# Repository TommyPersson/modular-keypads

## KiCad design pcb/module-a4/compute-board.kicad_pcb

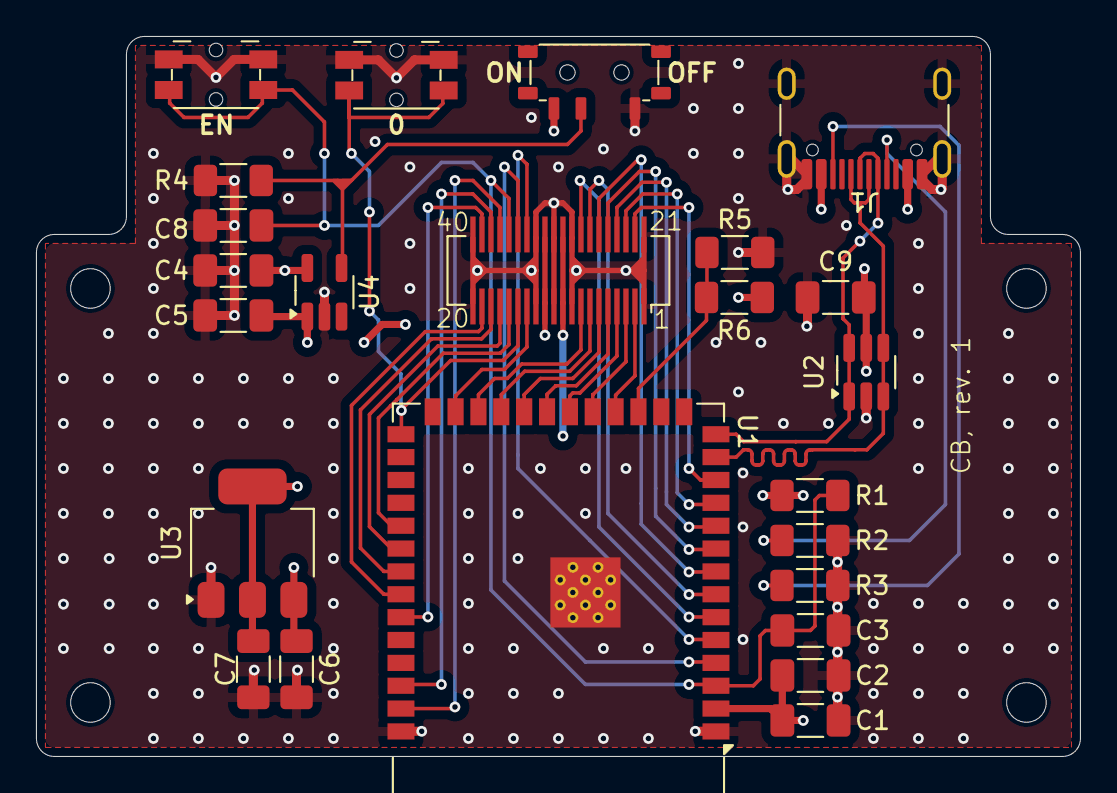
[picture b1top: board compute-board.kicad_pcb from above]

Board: 4 copper layers, 58.0 x 40.0 mm, 28 parts (0 on the bottom side), 36 nets.

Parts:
C1, C7: 22uF; C_1206_3216Metric_Pad1.33x1.80mm_HandSolder
C2, C4, C5, C8, C9: 0.1uF; C_1206_3216Metric_Pad1.33x1.80mm_HandSolder
C3: 1uF; C_1206_3216Metric_Pad1.33x1.80mm_HandSolder
C6: 10uF; C_1206_3216Metric_Pad1.33x1.80mm_HandSolder
H1, H2, H3, H4: MountingHole; MountingHole_2.2mm_M2
J1: USB_C_Receptacle_USB2.0_16P; USB_C_Receptacle_GCT_USB4105-xx-A_16P_TopMnt_Horizontal
J2: Conn_02x20; Hirose_DF12_DF12C3.0-40DS-0.5V_2x20_P0.50mm_Vertical
R1, R4, R5: 10k; R_1206_3216Metric_Pad1.30x1.75mm_HandSolder
R2, R3: 5.1K; R_1206_3216Metric_Pad1.30x1.75mm_HandSolder
R6: 5.1k; R_1206_3216Metric_Pad1.30x1.75mm_HandSolder
SW1: SW_Push_SPDT; SW_MSK12C02-HB
SW2, SW3: SW_Push; Panasonic_EVQPUL_EVQPUC
U1: ESP32-S3-WROOM-1
U2: USBLC6-2SC6; SOT-23-6_Handsoldering
U3: LD1117-3.3H; SOT-223-3_TabPin2
U4: AP2151W; SOT-23-5_HandSoldering

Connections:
+3.3V: C1.1, C2.1, C7.1, J2.10, J2.30, R1.1, U1.2 (3V3), U3.2 (VO)
+5V: C5.1, C6.1, J2.12, J2.32, U3.3 (VI), U4.1 (OUT)
/EN: C3.1, C8.2, J2.36, R1.2, SW2.2, U1.3 (EN)
/EX1: J2.7, U1.23 (IO21)
/EX2: J2.8, U1.24 (IO47)
/IO0: J2.15, SW3.2, U1.27 (IO0)
/IO1: J2.37, U1.39 (IO1)
/IO2: J2.38, U1.38 (IO2)
/IO4: J2.35, U1.4 (IO4)
/IO5: J2.34, U1.5 (IO5)
/IO6: J2.28, U1.6 (IO6)
/IO7: J2.27, U1.7 (IO7)
/IO8: J2.22, U1.12 (IO8)
/IO15: J2.26, U1.8 (IO15)
/IO16: J2.25, U1.9 (IO16)
/IO17: J2.24, U1.10 (IO17)
/IO18: J2.23, U1.11 (IO18)
/IO38: J2.16, U1.31 (IO38)
/IO39: J2.17, U1.32 (IO39)
/IO40: J2.18, U1.33 (IO40)
/IO41: J2.19, U1.34 (IO41)
/IO42: J2.39, U1.35 (IO42)
/IO48: J2.14, U1.25 (IO48)
/MISO: J2.5, U1.21 (IO13)
/MOSI: J2.6, U1.22 (IO14)
/SCK: J2.4, U1.20 (IO12)
/SCL: J2.2, U1.18 (IO10)
/SDA: J2.3, U1.19 (IO11)
/VBUS_SENSE: R5.1, R6.2, U1.17 (IO9)
/power-distribution/AP_EN: R4.1, SW1.2 (B), U4.4 (EN)
/usb-c-connector/CC1: J1.A5 (CC1), R2.1
/usb-c-connector/CC2: J1.B5 (CC2), R3.1
GND: C1.2, C2.2, C3.2, C4.2, C5.2, C6.2, C7.2, C8.1, C9.2, J1.A1 (GND), J1.A12 (GND), J1.B1 (GND), J1.B12 (GND), J1.S1 (SHIELD), J2.1, J2.9, J2.11, J2.13, J2.20, J2.21, J2.29, J2.31, J2.33, J2.40, R2.2, R3.2, R4.2, R5.2, SW1.1 (A), SW2.1, SW3.1, U1.1 (GND), U1.40 (GND), U1.41 (GND), U2.2 (GND), U3.1 (GND), U4.2 (GND)
USB_D+: J1.A7 (D-), J1.B7 (D-), U1.14 (USB_D+), U2.1 (I/O1), U2.6 (I/O1)
USB_D-: J1.A6 (D+), J1.B6 (D+), U1.13 (USB_D-), U2.3 (I/O2), U2.4 (I/O2)
VBUS: C4.1, C9.1, J1.A4 (VBUS), J1.A9 (VBUS), J1.B4 (VBUS), J1.B9 (VBUS), R6.1, SW1.3 (C), U2.5 (VBUS), U4.5 (IN)

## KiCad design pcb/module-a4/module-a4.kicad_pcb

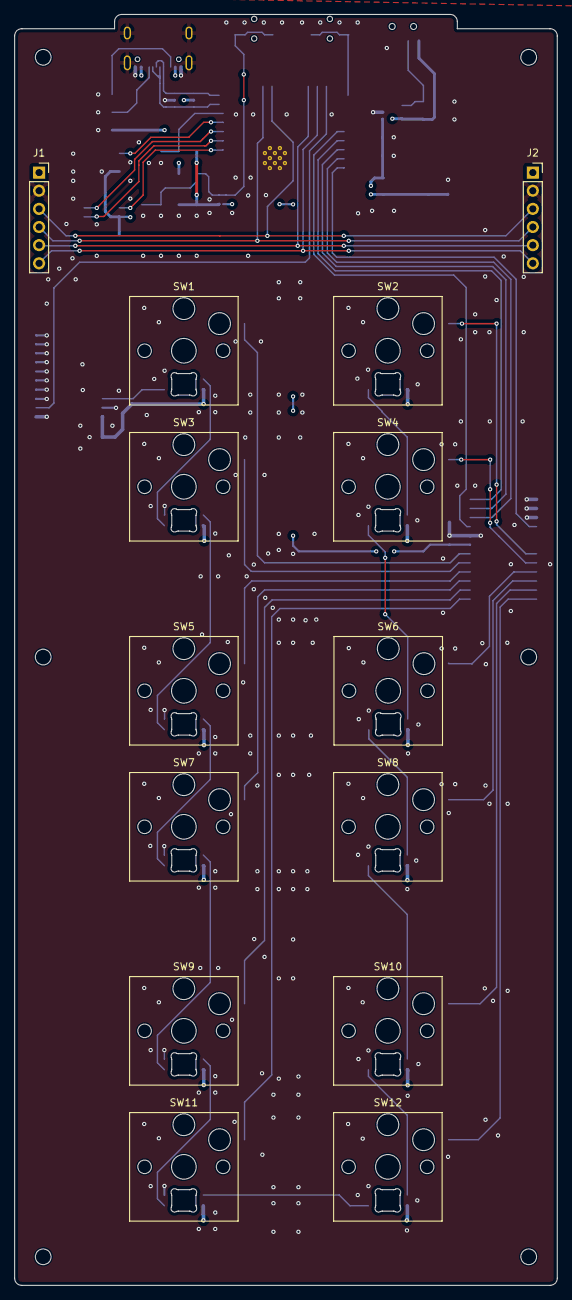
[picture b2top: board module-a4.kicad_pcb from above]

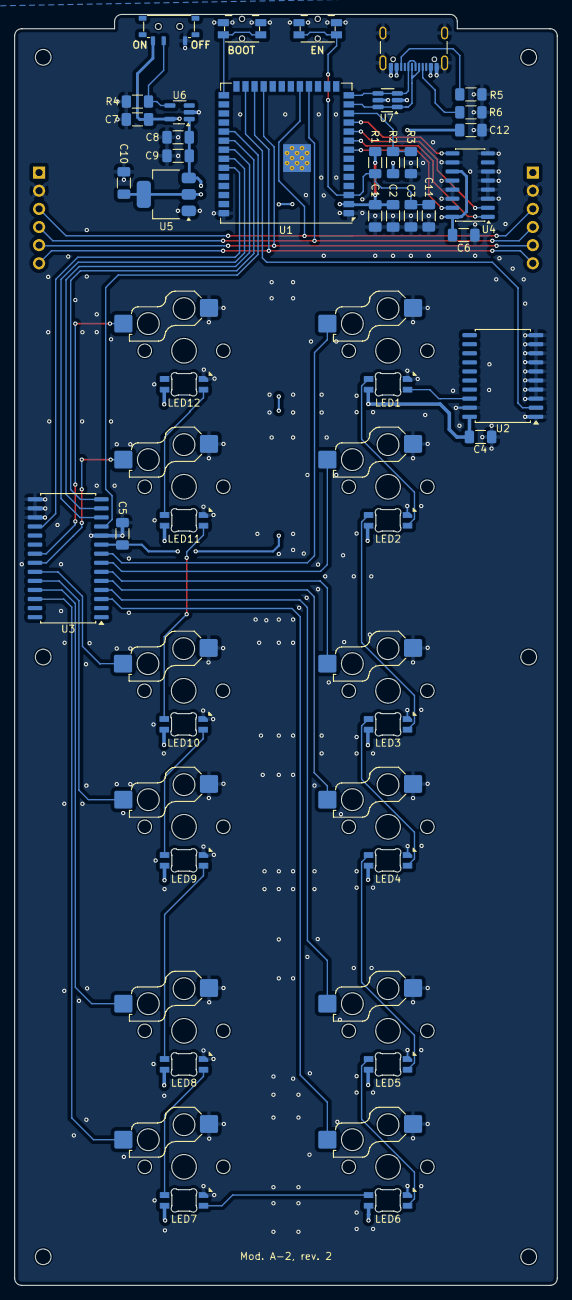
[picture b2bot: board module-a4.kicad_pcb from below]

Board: 4 copper layers, 76.0 x 178.0 mm, 61 parts (41 on the bottom side), 50 nets.

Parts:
C1, C10: 22uF; C_1206_3216Metric_Pad1.33x1.80mm_HandSolder
C2, C4, C5, C6, C7, C8, C11, C12: 0.1uF; C_1206_3216Metric_Pad1.33x1.80mm_HandSolder
C3: 1uF; C_1206_3216Metric_Pad1.33x1.80mm_HandSolder
C9: 10uF; C_1206_3216Metric_Pad1.33x1.80mm_HandSolder
H1, H2, H3, H4, H5, H6: MountingHole; MountingHole_2.2mm_M2
J1: Conn_01x06; PinSocket_1x06_P2.54mm_MagPogoHor_R
J2: Conn_01x06; PinSocket_1x06_P2.54mm_MagPogoHor
J3: USB_C_Receptacle_USB2.0_16P; USB_C_Receptacle_GCT_USB4105-xx-A_16P_TopMnt_Horizontal
LED1, LED2, LED3, LED4, LED5, LED6, LED7, LED8, LED9, LED10, LED11, LED12: SK6812MINI-E; LED_choc_6028R-ROT
R1, R3, R4: 10k; R_1206_3216Metric_Pad1.30x1.75mm_HandSolder
R2: 5.1k; R_1206_3216Metric_Pad1.30x1.75mm_HandSolder
R5, R6: 5.1K; R_1206_3216Metric_Pad1.30x1.75mm_HandSolder
SW1, SW2, SW3, SW4, SW5, SW6, SW7, SW8, SW9, SW10, SW11, SW12: SW_Push; SW_Hotswap_Kailh_Choc_V1_1.50u
SW13: SW_Push_SPDT; SW_MSK12C02-HB
SW14, SW15: SW_Push; Panasonic_EVQPUL_EVQPUC
U1: ESP32-S3-WROOM-1; ESP32-S3-WROOM-1U
U2: 74AHC541; SOIC-20W_7.5x12.8mm_P1.27mm
U3: MCP23S17_SO; SOIC-28W_7.5x17.9mm_P1.27mm
U4: 74HC165; SOIC-16_3.9x9.9mm_P1.27mm
U5: LD1117-3.3H; SOT-223-3_TabPin2
U6: AP2151W; SOT-23-5_HandSoldering
U7: USBLC6-2SC6; SOT-23-6_Handsoldering

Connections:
+3.3V: C1.1, C2.1, C5.1, C6.1, C10.1, R1.1, U1.2 (3V3), U3.9 (VDD), U4.11 (D0), U4.16 (VCC), U5.2 (VO)
+5V: C4.1, C8.1, C9.1, J1.1, J2.1, LED1.1 (VDD), LED2.1 (VDD), LED3.1 (VDD), LED4.1 (VDD), LED5.1 (VDD), LED6.1 (VDD), LED7.1 (VDD), LED8.1 (VDD), LED9.1 (VDD), LED10.1 (VDD), LED11.1 (VDD), LED12.1 (VDD), U2.20 (VCC), U5.3 (VI), U6.1 (OUT)
/A0: SW2.2, U3.21 (GPA0)
/A1: SW4.2, U3.22 (GPA1)
/A2: SW6.2, U3.23 (GPA2)
/A3: SW8.2, U3.24 (GPA3)
/A4: SW10.2, U3.25 (GPA4)
/A5: SW12.2, U3.26 (GPA5)
/B2: SW11.2, U3.3 (GPB2)
/B3: SW9.2, U3.4 (GPB3)
/B4: SW7.2, U3.5 (GPB4)
/B5: SW5.2, U3.6 (GPB5)
/B6: SW3.2, U3.7 (GPB6)
/B7: SW1.2, U3.8 (GPB7)
/EN: C3.1, C11.2, R1.2, SW14.2, U1.3 (EN)
/EX1: J1.5, J2.5, U1.23 (IO21)
/EX2: J1.6, J2.6, U1.24 (IO47)
/IO0: SW15.2, U1.27 (IO0)
/IO48: U1.25 (IO48), U2.2 (A0)
/MISO: U1.32 (IO39), U3.14 (SO)
/MOSI: U1.33 (IO40), U3.13 (SI)
/SCK: U1.34 (IO41), U3.12 (SCK)
/SCL: J1.4, J2.4, U1.18 (IO10)
/SDA: J1.3, J2.3, U1.19 (IO11)
/TREG_CP: U1.10 (IO17), U4.2 (CP)
/TREG_Q: U1.11 (IO18), U4.9 (Q7)
/VBUS_SENSE: R2.2, R3.1, U1.12 (IO8)
/power-distribution/AP_EN: R4.1, SW13.2 (B), U6.4 (EN)
/usb-c-connector/CC1: J3.A5 (CC1), R6.1
/usb-c-connector/CC2: J3.B5 (CC2), R5.1
/~MCP_CS: U1.31 (IO38), U3.11 (~CS)
/~MCP_RESET: U1.35 (IO42), U3.18 (~RESET)
/~TREG_CE: U1.8 (IO15), U4.15 (~CE)
/~TREG_PL: U1.9 (IO16), U4.1 (~PL)
GND: C1.2, C2.2, C3.2, C4.2, C5.2, C6.2, C7.2, C8.2, C9.2, C10.2, C11.1, C12.2, J1.2, J2.2, J3.A1 (GND), J3.A12 (GND), J3.B1 (GND), J3.B12 (GND), J3.S1 (SHIELD), LED1.4 (VSS), LED2.4 (VSS), LED3.4 (VSS), LED4.4 (VSS), LED5.4 (VSS), LED6.4 (VSS), LED7.4 (VSS), LED8.4 (VSS), LED9.4 (VSS), LED10.4 (VSS), LED11.4 (VSS), LED12.4 (VSS), R3.2, R4.2, R5.2, R6.2, SW1.1, SW2.1, SW3.1, SW4.1, SW5.1, SW6.1, SW7.1, SW8.1, SW9.1, SW10.1, SW11.1, SW12.1, SW13.1 (A), SW14.1, SW15.1, U1.1 (GND), U1.40 (GND), U1.41 (GND), U2.1 (G1), U2.3 (A1), U2.4 (A2), U2.5 (A3), U2.6 (A4), U2.7 (A5), U2.8 (A6), U2.9 (A7), U2.10 (GND), U2.19 (G2), U3.10 (VSS), U3.15 (A0), U3.16 (A1), U3.17 (A2), U4.3 (D4), U4.4 (D5), U4.5 (D6), U4.6 (D7), U4.8 (GND), U4.10 (DS), U4.12 (D1), U4.13 (D2), U4.14 (D3), U5.1 (GND), U6.2 (GND), U7.2 (GND)
unnamed: LED1.3 (DIN), U2.18 (Y0)
unnamed: LED1.2 (DOUT), LED2.3 (DIN)
unnamed: LED2.2 (DOUT), LED3.3 (DIN)
unnamed: LED3.2 (DOUT), LED4.3 (DIN)
unnamed: LED4.2 (DOUT), LED5.3 (DIN)
unnamed: LED5.2 (DOUT), LED6.3 (DIN)
unnamed: LED6.2 (DOUT), LED7.3 (DIN)
unnamed: LED7.2 (DOUT), LED8.3 (DIN)
unnamed: LED8.2 (DOUT), LED9.3 (DIN)
unnamed: LED9.2 (DOUT), LED10.3 (DIN)
unnamed: LED10.2 (DOUT), LED11.3 (DIN)
unnamed: LED11.2 (DOUT), LED12.3 (DIN)
USB_D+: J3.A6 (D+), J3.B6 (D+), U1.14 (USB_D+), U7.3 (I/O2), U7.4 (I/O2)
USB_D-: J3.A7 (D-), J3.B7 (D-), U1.13 (USB_D-), U7.1 (I/O1), U7.6 (I/O1)
VBUS: C7.1, C12.1, J3.A4 (VBUS), J3.A9 (VBUS), J3.B4 (VBUS), J3.B9 (VBUS), R2.1, SW13.3 (C), U6.5 (IN), U7.5 (VBUS)

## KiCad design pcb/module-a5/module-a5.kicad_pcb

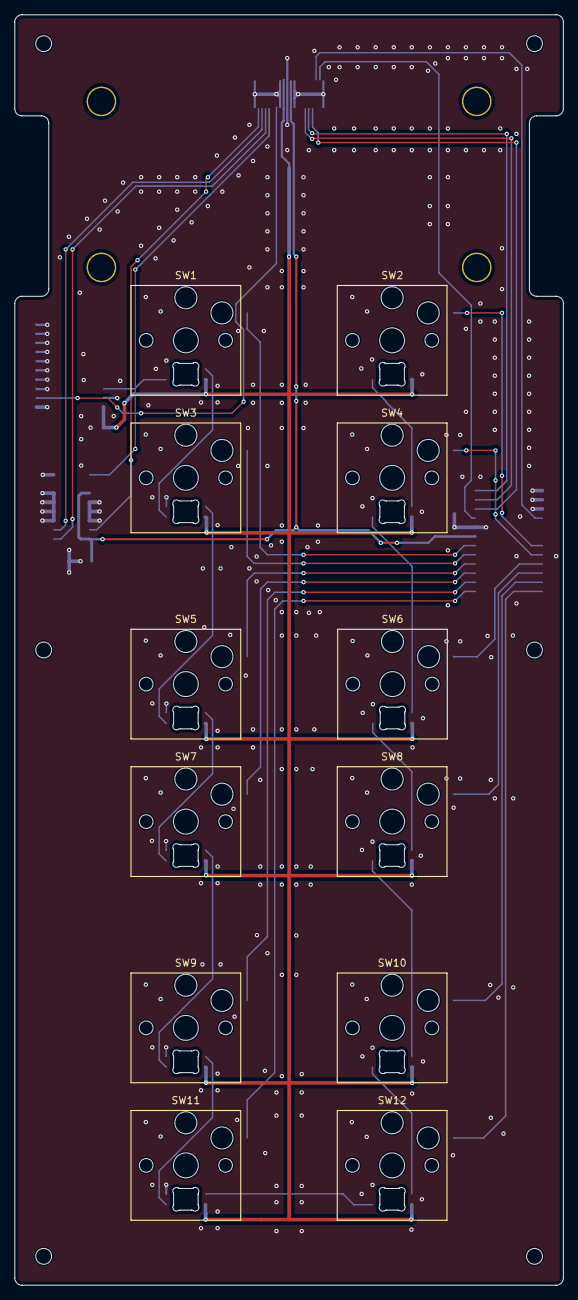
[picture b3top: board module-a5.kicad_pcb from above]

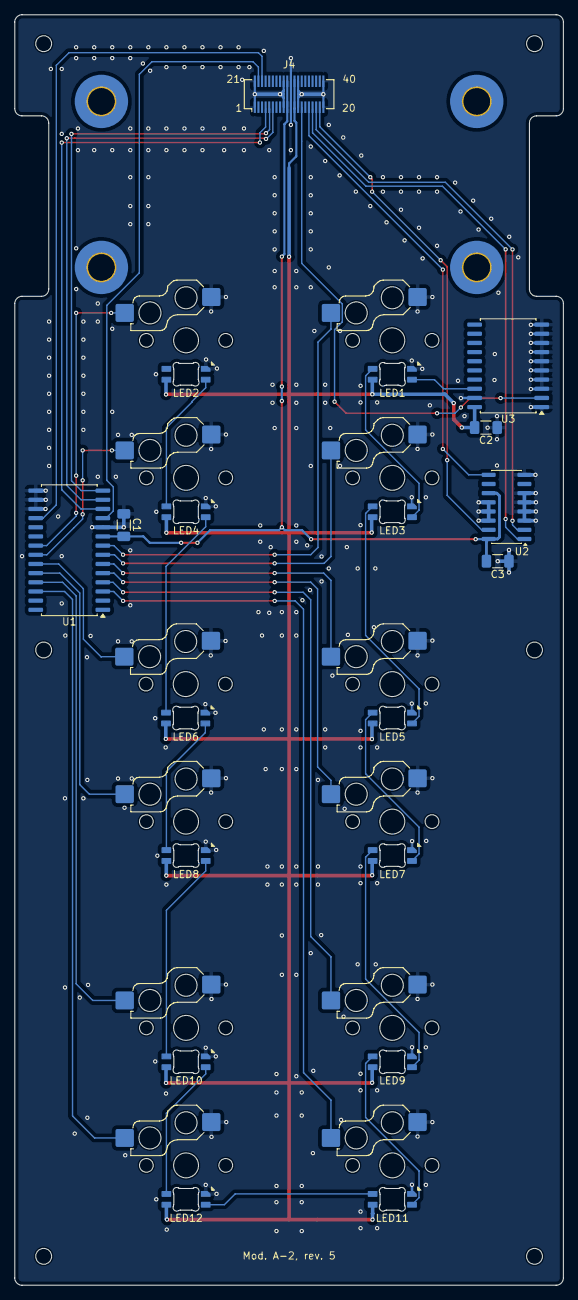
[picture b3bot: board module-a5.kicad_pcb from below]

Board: 2 copper layers, 76.0 x 176.0 mm, 41 parts (23 on the bottom side), 37 nets.

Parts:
C1, C2, C3: 0.1uF; C_1206_3216Metric_Pad1.33x1.80mm_HandSolder
H1, H2, H3, H4, H5, H6: MountingHole; MountingHole_2.2mm_M2
H7, H8, H9, H10: MountingHole; MountingHole_3.7mm_Pad_TopOnly
J4: Conn_02x20_Top_Bottom; Hirose_DF12_DF12E3.0-40DP-0.5V_2x20_P0.50mm_Vertical
LED1, LED2, LED3, LED4, LED5, LED6, LED7, LED8, LED9, LED10, LED11, LED12: SK6812MINI-E; LED_choc_6028R-ROT
SW1, SW2, SW3, SW4, SW5, SW6, SW7, SW8, SW9, SW10, SW11, SW12: SW_Push; SW_Hotswap_Kailh_Choc_V1_1.50u
U1: MCP23S17_SO; SOIC-28W_7.5x17.9mm_P1.27mm
U2: 74HC165; SOIC-16_3.9x9.9mm_P1.27mm
U3: 74AHC541; SOIC-20W_7.5x12.8mm_P1.27mm

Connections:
+3.3V: C1.1, C3.1, J4.10, J4.30, U1.9 (VDD), U2.11 (D0), U2.16 (VCC)
+5V: C2.1, J4.12, J4.32, LED1.1 (VDD), LED2.1 (VDD), LED3.1 (VDD), LED4.1 (VDD), LED5.1 (VDD), LED6.1 (VDD), LED7.1 (VDD), LED8.1 (VDD), LED9.1 (VDD), LED10.1 (VDD), LED11.1 (VDD), LED12.1 (VDD), U3.20 (VCC)
/A0: SW2.2, U1.21 (GPA0)
/A1: SW4.2, U1.22 (GPA1)
/A2: SW6.2, U1.23 (GPA2)
/A3: SW8.2, U1.24 (GPA3)
/A4: SW10.2, U1.25 (GPA4)
/A5: SW12.2, U1.26 (GPA5)
/B2: SW11.2, U1.3 (GPB2)
/B3: SW9.2, U1.4 (GPB3)
/B4: SW7.2, U1.5 (GPB4)
/B5: SW5.2, U1.6 (GPB5)
/B6: SW3.2, U1.7 (GPB6)
/B7: SW1.2, U1.8 (GPB7)
/IO8: J4.22, U1.11 (~CS)
/IO18: J4.23, U1.18 (~RESET)
/IO38: J4.16, U2.9 (Q7)
/IO39: J4.17, U2.1 (~PL)
/IO40: J4.18, U2.2 (CP)
/IO41: J4.19, U2.15 (~CE)
/IO48: J4.14, U3.2 (A0)
/MISO: J4.5, U1.14 (SO)
/MOSI: J4.6, U1.13 (SI)
/SCK: J4.4, U1.12 (SCK)
GND: C1.2, C2.2, C3.2, J4.1, J4.9, J4.11, J4.13, J4.20, J4.21, J4.29, J4.31, J4.33, J4.40, LED1.4 (VSS), LED2.4 (VSS), LED3.4 (VSS), LED4.4 (VSS), LED5.4 (VSS), LED6.4 (VSS), LED7.4 (VSS), LED8.4 (VSS), LED9.4 (VSS), LED10.4 (VSS), LED11.4 (VSS), LED12.4 (VSS), SW1.1, SW2.1, SW3.1, SW4.1, SW5.1, SW6.1, SW7.1, SW8.1, SW9.1, SW10.1, SW11.1, SW12.1, U1.10 (VSS), U1.15 (A0), U1.16 (A1), U1.17 (A2), U2.3 (D4), U2.4 (D5), U2.5 (D6), U2.6 (D7), U2.8 (GND), U2.12 (D1), U2.13 (D2), U2.14 (D3), U3.1 (G1), U3.3 (A1), U3.4 (A2), U3.5 (A3), U3.6 (A4), U3.7 (A5), U3.8 (A6), U3.9 (A7), U3.10 (GND), U3.19 (G2)
unnamed: LED1.3 (DIN), U3.18 (Y0)
unnamed: LED1.2 (DOUT), LED3.3 (DIN)
unnamed: LED2.3 (DIN), LED4.2 (DOUT)
unnamed: LED3.2 (DOUT), LED5.3 (DIN)
unnamed: LED4.3 (DIN), LED6.2 (DOUT)
unnamed: LED5.2 (DOUT), LED7.3 (DIN)
unnamed: LED6.3 (DIN), LED8.2 (DOUT)
unnamed: LED7.2 (DOUT), LED9.3 (DIN)
unnamed: LED10.3 (DIN), LED12.2 (DOUT)
unnamed: LED8.3 (DIN), LED10.2 (DOUT)
unnamed: LED9.2 (DOUT), LED11.3 (DIN)
unnamed: LED11.2 (DOUT), LED12.3 (DIN)

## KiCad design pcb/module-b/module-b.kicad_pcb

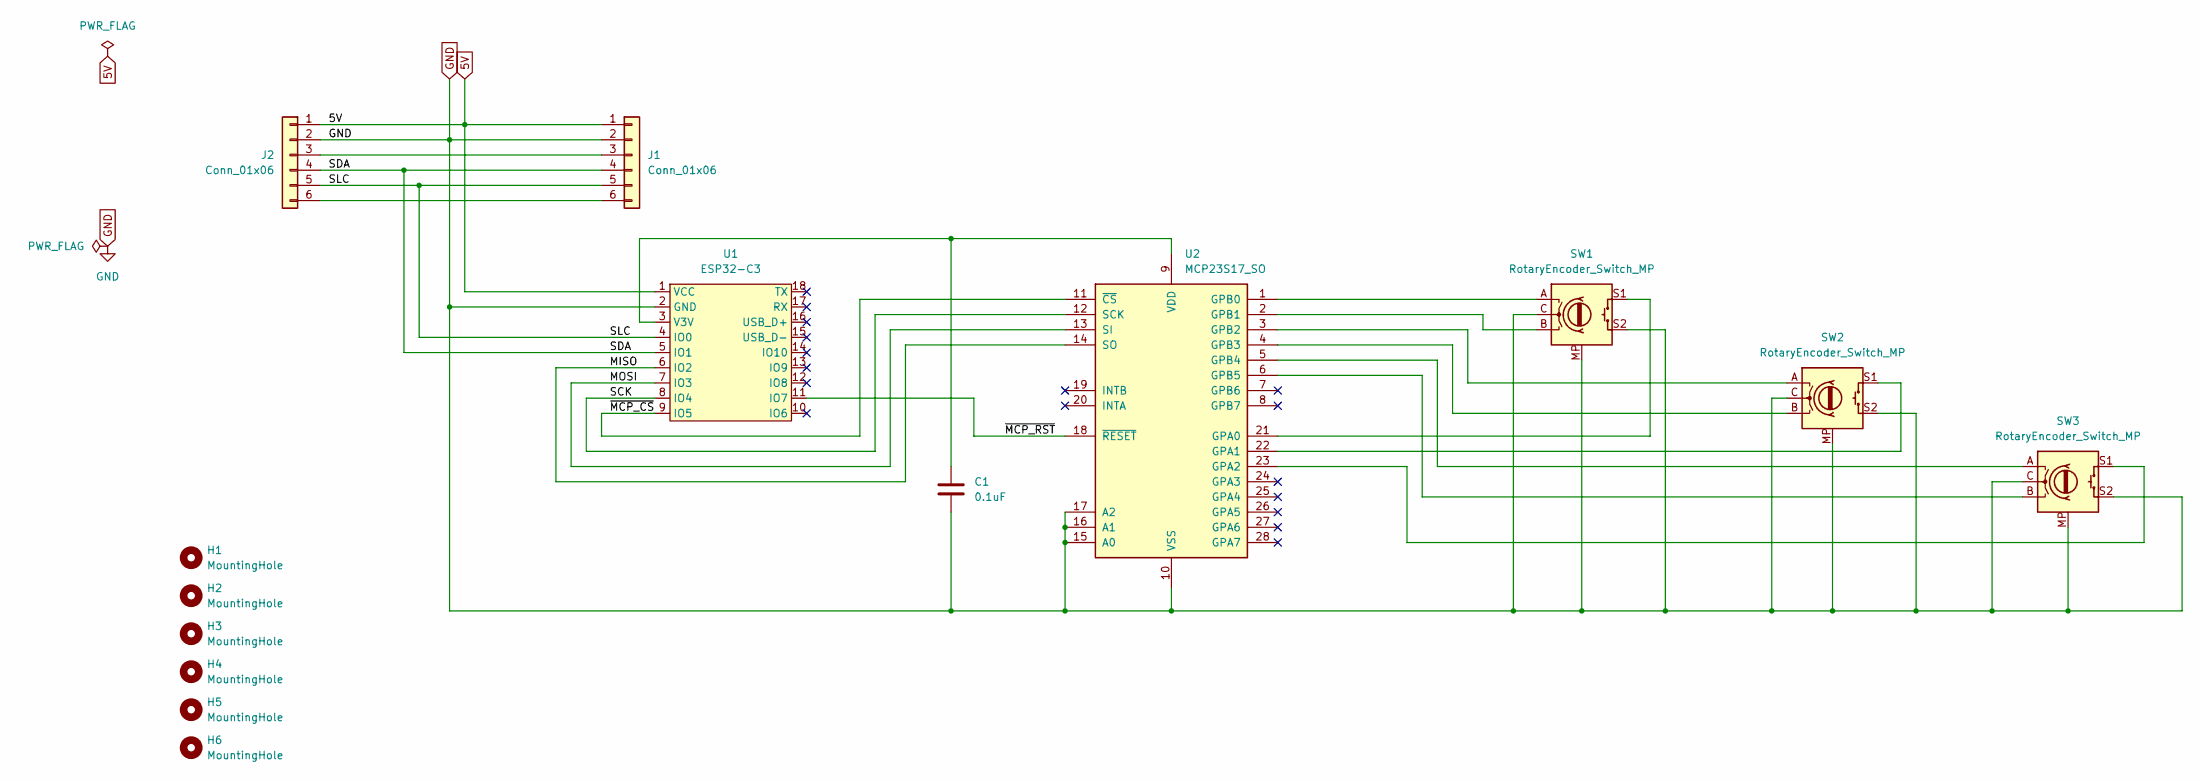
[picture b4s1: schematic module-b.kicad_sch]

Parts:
C1: 0.1uF; C_1206_3216Metric_Pad1.33x1.80mm_HandSolder
H1, H2, H3, H4, H5, H6: MountingHole; MountingHole_2.2mm_M2
J1: Conn_01x06; PinSocket_1x06_P2.54mm_MagPogoHor
J2: Conn_01x06; PinSocket_1x06_P2.54mm_MagPogoHor_R
SW1, SW2, SW3: RotaryEncoder_Switch_MP; RotaryEncoder_Alps_EC11E-Switch_Vertical_H20mm
U1: ESP32-C3; Waveshare-ESP32-C3-Zero
U2: MCP23S17_SO; SOIC-28W_7.5x17.9mm_P1.27mm

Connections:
5V: J1.1, J2.1, U1.1 (VCC)
/MISO: U1.6 (IO2), U2.14 (SO)
/MOSI: U1.7 (IO3), U2.13 (SI)
/SCK: U1.8 (IO4), U2.12 (SCK)
/SDA: J1.4, J2.4, U1.5 (IO1)
/SLC: J1.5, J2.5, U1.4 (IO0)
/~MCP_CS: U1.9 (IO5), U2.11 (~CS)
/~MCP_RST: U1.11 (IO7), U2.18 (~RESET)
GND: C1.2, J1.2, J2.2, SW1.C, SW1.MP, SW1.S2, SW2.C, SW2.MP, SW2.S2, SW3.C, SW3.MP, SW3.S2, U1.2 (GND), U2.10 (VSS), U2.15 (A0), U2.16 (A1), U2.17 (A2)
unnamed: J1.3, J2.3
unnamed: J1.6, J2.6
unnamed: C1.1, U1.3 (V3V), U2.9 (VDD)
unnamed: SW1.S1, U2.21 (GPA0)
unnamed: SW2.S1, U2.22 (GPA1)
unnamed: SW3.S1, U2.23 (GPA2)
unnamed: SW1.A, U2.1 (GPB0)
unnamed: SW1.B, U2.2 (GPB1)
unnamed: SW2.A, U2.3 (GPB2)
unnamed: SW2.B, U2.4 (GPB3)
unnamed: SW3.A, U2.5 (GPB4)
unnamed: SW3.B, U2.6 (GPB5)

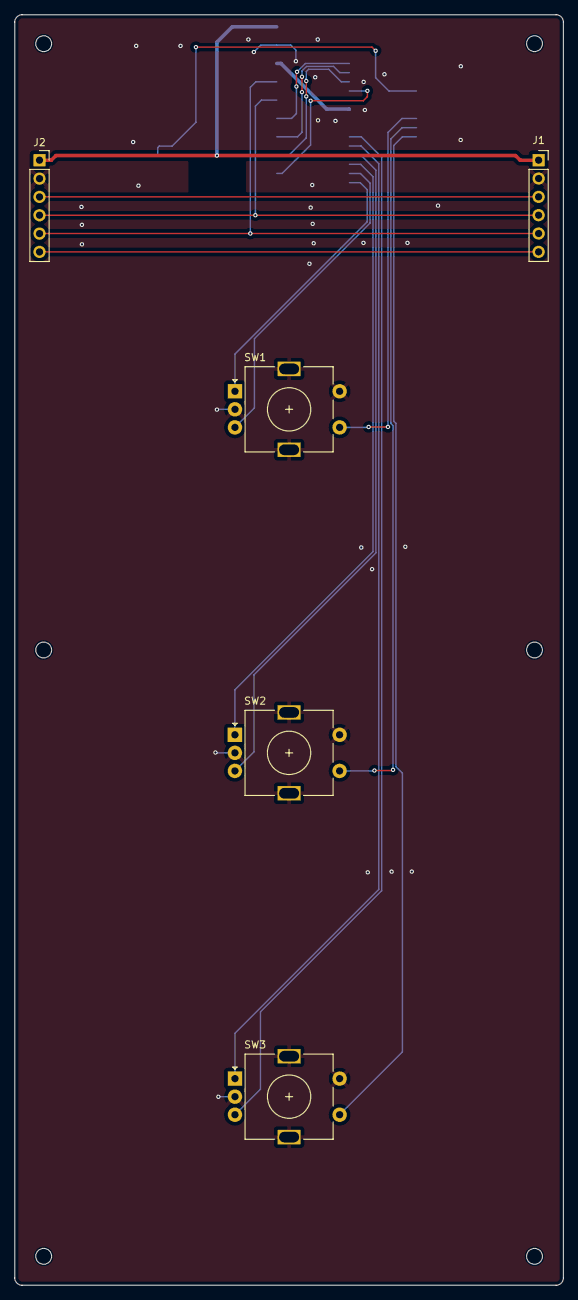
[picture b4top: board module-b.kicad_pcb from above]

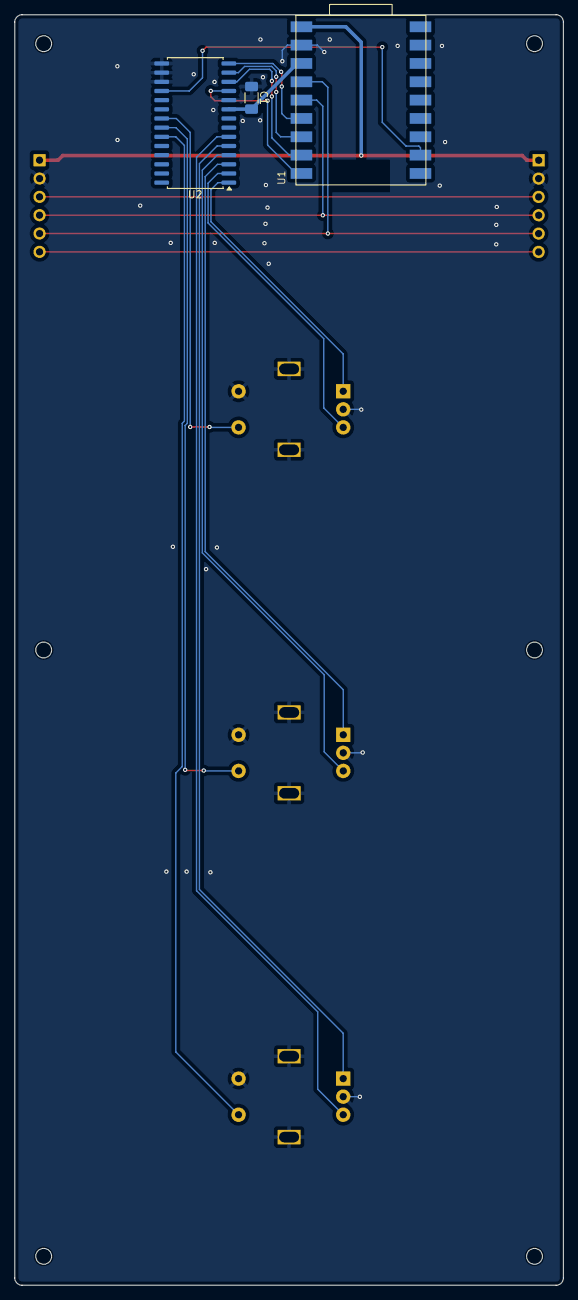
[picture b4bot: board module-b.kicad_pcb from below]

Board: 2 copper layers, 76.0 x 176.0 mm, 14 parts (3 on the bottom side), 21 nets.

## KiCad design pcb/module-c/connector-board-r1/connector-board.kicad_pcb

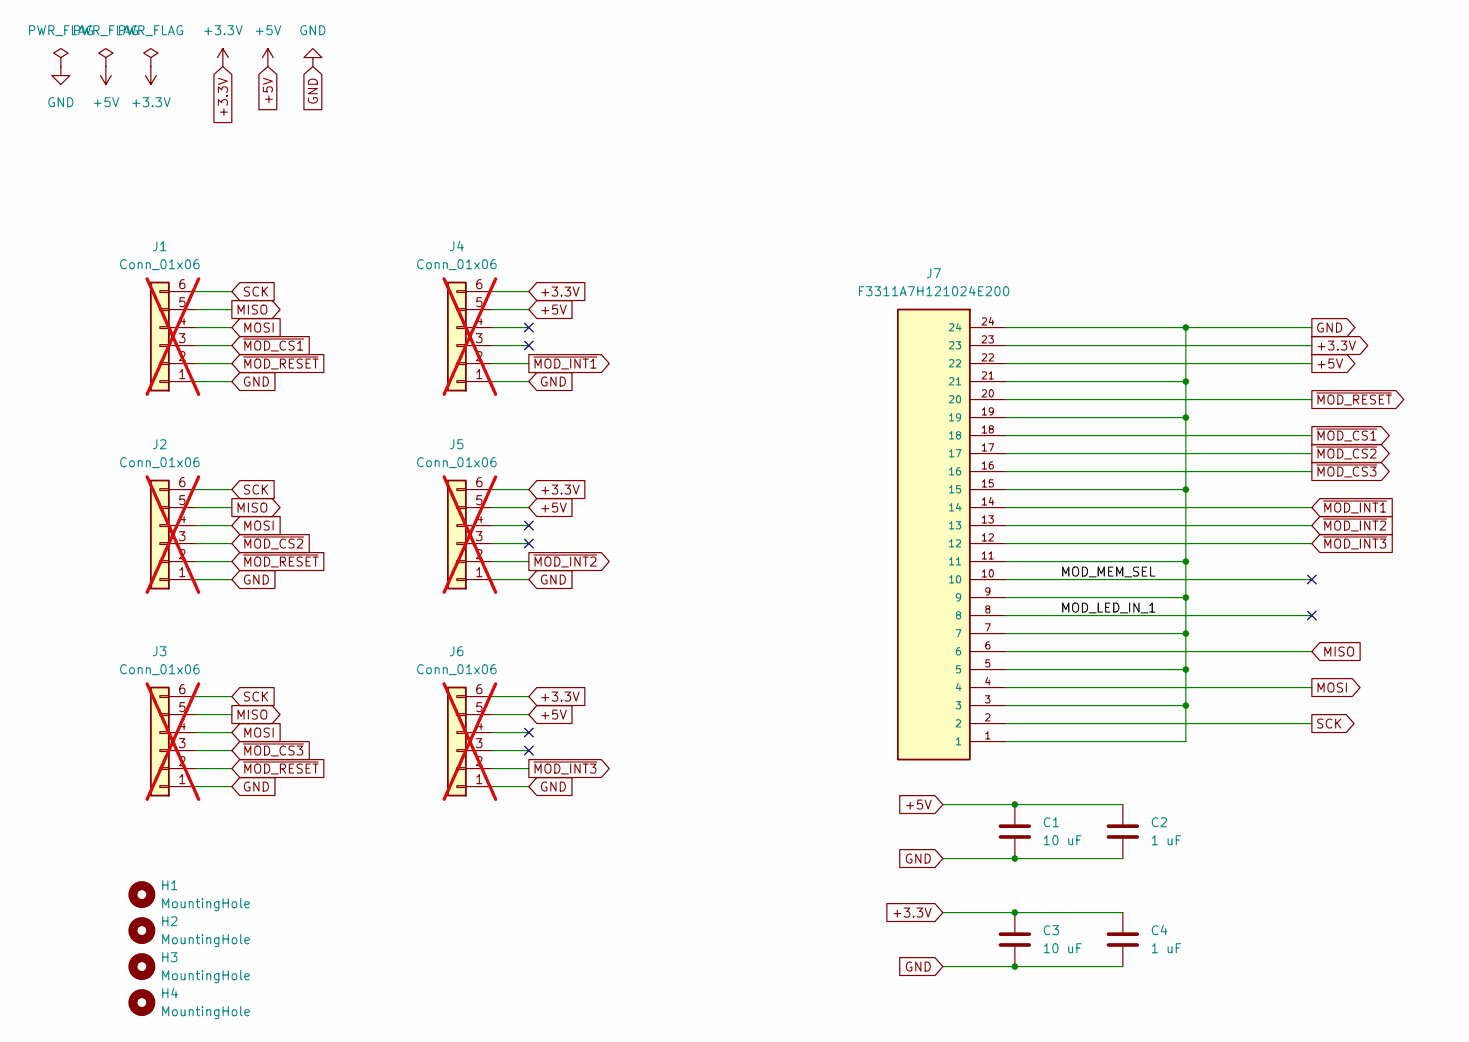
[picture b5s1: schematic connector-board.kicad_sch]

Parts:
C1, C3: 10 uF; C_1206_3216Metric
C2, C4: 1 uF; C_1206_3216Metric
H1, H2, H3, H4: MountingHole; MountingHole_2.2mm_M2
J1, J2, J3, J4, J5, J6: Conn_01x06; PinHeader_1x06_P2.54mm_Vertical; not fitted
J7: F3311A7H121024E200; AMPHENOL_F3311A7H121024E200; PARTREV A

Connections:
+3.3V: C3.1, C4.1, J4.6, J5.6, J6.6, J7.23
+5V: C1.1, C2.1, J4.5, J5.5, J6.5, J7.22
/MOD_LED_IN_1: J7.8
/MOD_MEM_SEL: J7.10
GND: C1.2, C2.2, C3.2, C4.2, J1.1, J2.1, J3.1, J4.1, J5.1, J6.1, J7.1, J7.3, J7.5, J7.7, J7.9, J7.11, J7.15, J7.19, J7.21, J7.24
MISO: J1.5, J2.5, J3.5, J7.6
MOSI: J1.4, J2.4, J3.4, J7.4
SCK: J1.6, J2.6, J3.6, J7.2
~MOD_CS1: J1.3, J7.18
~MOD_CS2: J2.3, J7.17
~MOD_CS3: J3.3, J7.16
~MOD_INT1: J4.2, J7.14
~MOD_INT2: J5.2, J7.13
~MOD_INT3: J6.2, J7.12
~MOD_RESET: J1.2, J2.2, J3.2, J7.20

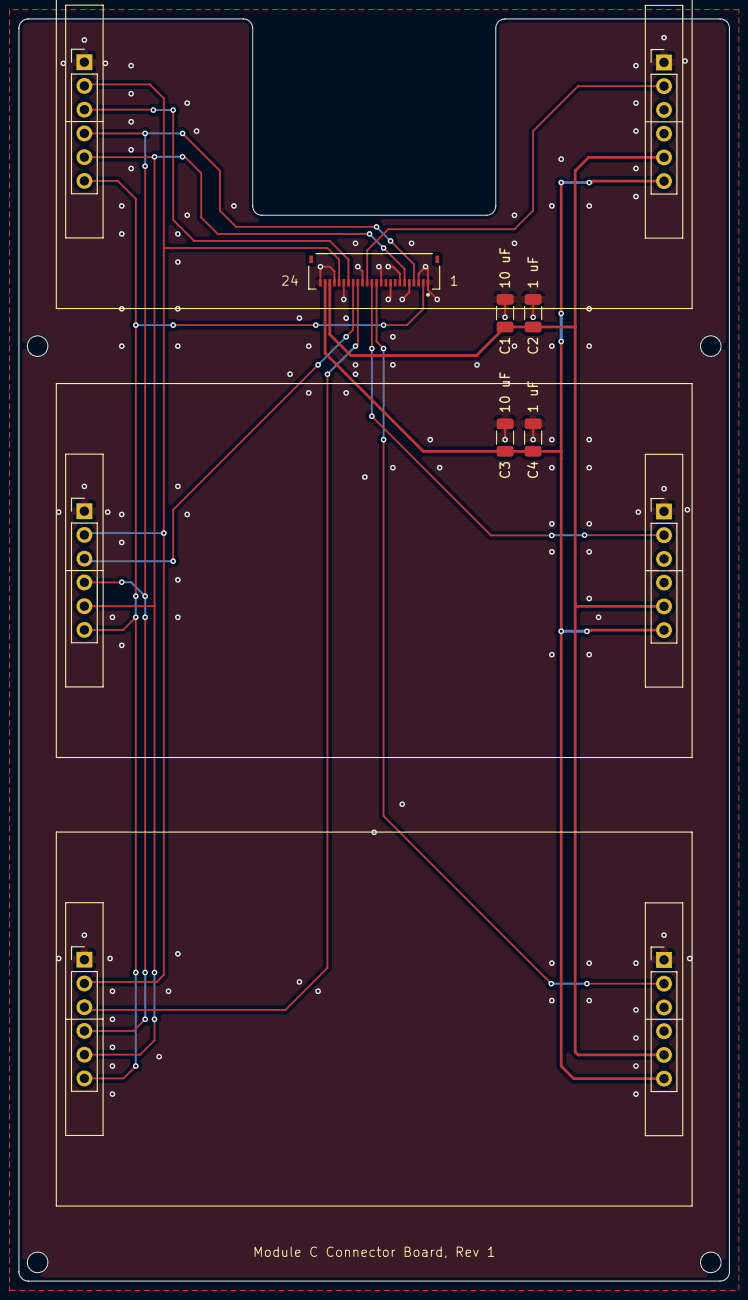
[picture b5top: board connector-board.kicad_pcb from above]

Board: 2 copper layers, 76.0 x 135.0 mm, 15 parts (0 on the bottom side), 13 nets.

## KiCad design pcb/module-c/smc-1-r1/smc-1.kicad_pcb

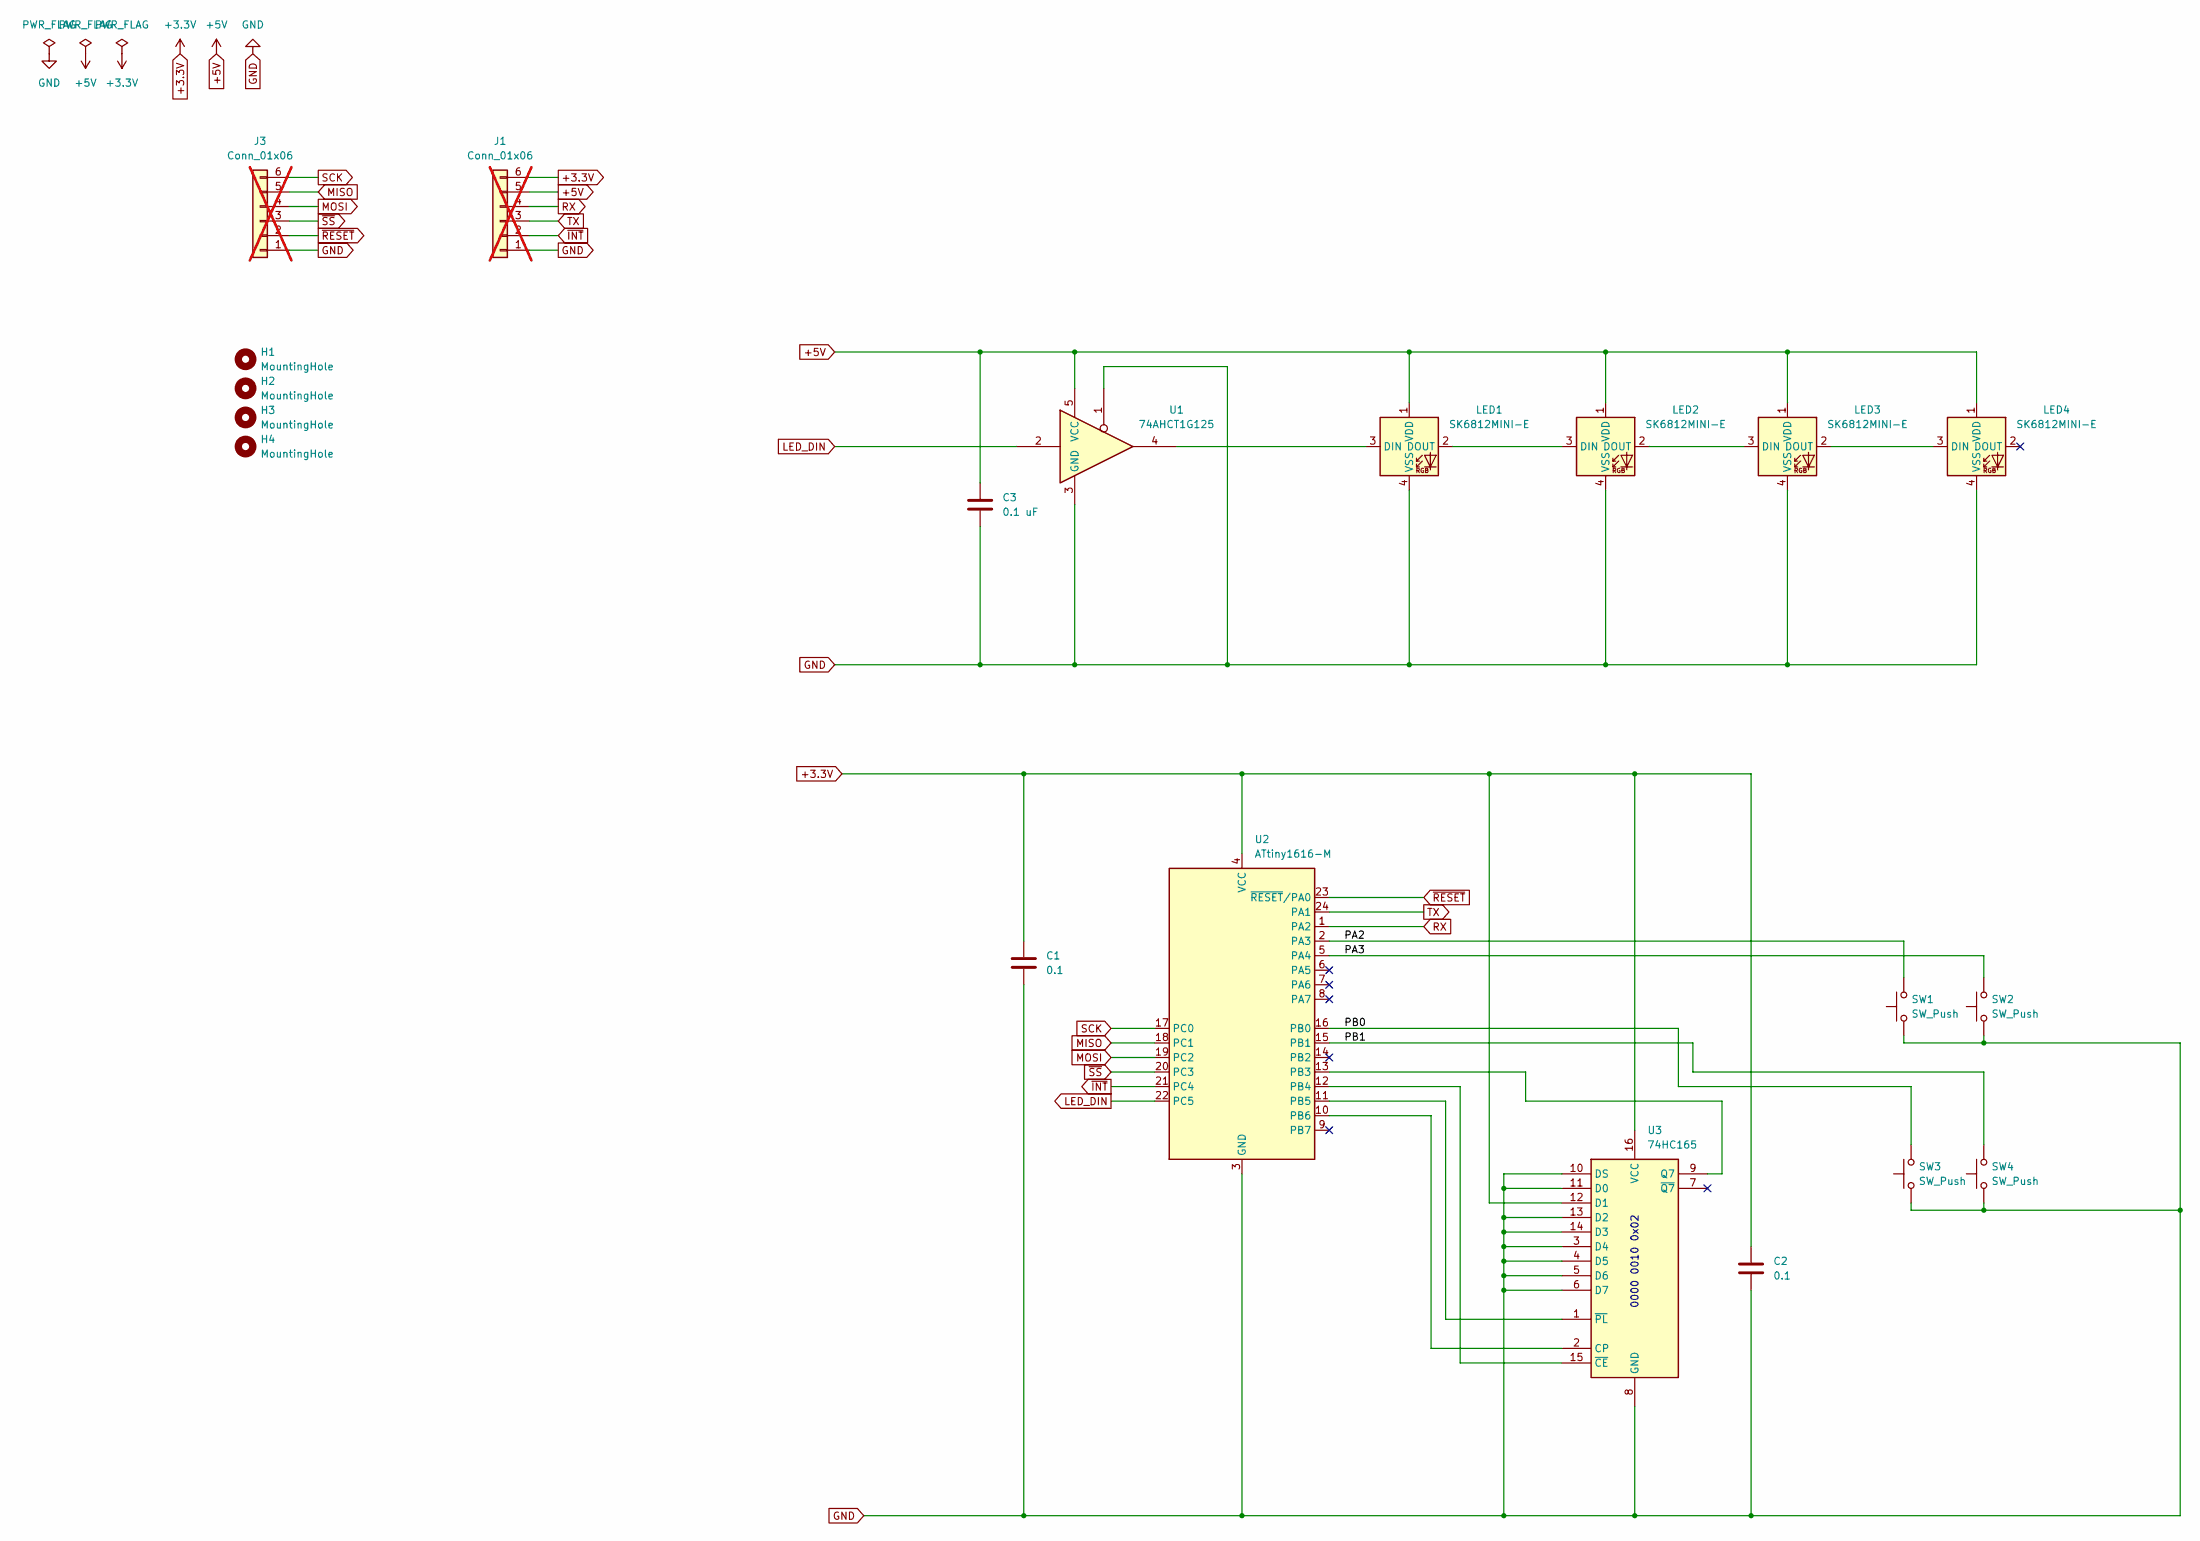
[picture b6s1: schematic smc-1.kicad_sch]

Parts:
C1, C2: 0.1; C_0603_1608Metric
C3: 0.1 uF; C_0603_1608Metric
H1, H2, H3, H4: MountingHole; MountingHole_2.2mm_M2
J1, J3: Conn_01x06; PinHeader_1x06_P2.54mm_Vertical; not fitted
LED1, LED2, LED3, LED4: SK6812MINI-E; LED_choc_6028R-ROT
SW1, SW2, SW3, SW4: SW_Push; SW_Hotswap_Kailh_Choc_V1_1.50u
U1: 74AHCT1G125; SOT-353_SC-70-5
U2: ATtiny1616-M; QFN-24-1EP_4x4mm_P0.5mm_EP2.6x2.6mm
U3: 74HC165; DHVQFN-16-1EP_2.5x3.5mm_P0.5mm_EP1x2mm

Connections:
+3.3V: C1.1, C2.1, J1.6, U2.4 (VCC), U3.12 (D1), U3.16 (VCC)
+5V: C3.1, J1.5, LED1.1 (VDD), LED2.1 (VDD), LED3.1 (VDD), LED4.1 (VDD), U1.5 (VCC)
/PA2: SW1.2, U2.2 (PA3)
/PA3: SW2.2, U2.5 (PA4)
/PB0: SW3.2, U2.16 (PB0)
/PB1: SW4.2, U2.15 (PB1)
GND: C1.2, C2.2, C3.2, J1.1, J3.1, LED1.4 (VSS), LED2.4 (VSS), LED3.4 (VSS), LED4.4 (VSS), SW1.1, SW2.1, SW3.1, SW4.1, U1.1, U1.3 (GND), U2.3 (GND), U2.25 (GND), U3.3 (D4), U3.4 (D5), U3.5 (D6), U3.6 (D7), U3.8 (GND), U3.10 (DS), U3.11 (D0), U3.13 (D2), U3.14 (D3)
LED_DIN: U1.2, U2.22 (PC5)
MISO: J3.5, U2.18 (PC1)
MOSI: J3.4, U2.19 (PC2)
unnamed: LED1.3 (DIN), U1.4
unnamed: LED1.2 (DOUT), LED2.3 (DIN)
unnamed: LED2.2 (DOUT), LED3.3 (DIN)
unnamed: LED3.2 (DOUT), LED4.3 (DIN)
unnamed: U2.13 (PB3), U3.9 (Q7)
unnamed: U2.12 (PB4), U3.15 (~CE)
unnamed: U2.11 (PB5), U3.1 (~PL)
unnamed: U2.10 (PB6), U3.2 (CP)
RX: J1.4, U2.1 (PA2)
SCK: J3.6, U2.17 (PC0)
TX: J1.3, U2.24 (PA1)
~INT: J1.2, U2.21 (PC4)
~RESET: J3.2, U2.23 (~RESET/PA0)
~SS: J3.3, U2.20 (PC3)

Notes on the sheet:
0000 0010 0x02
